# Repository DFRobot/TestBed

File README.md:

TestBed 
=======

Author: Leo Yan.

=======

It is used to test board. It is not a product.

=======
V1.0

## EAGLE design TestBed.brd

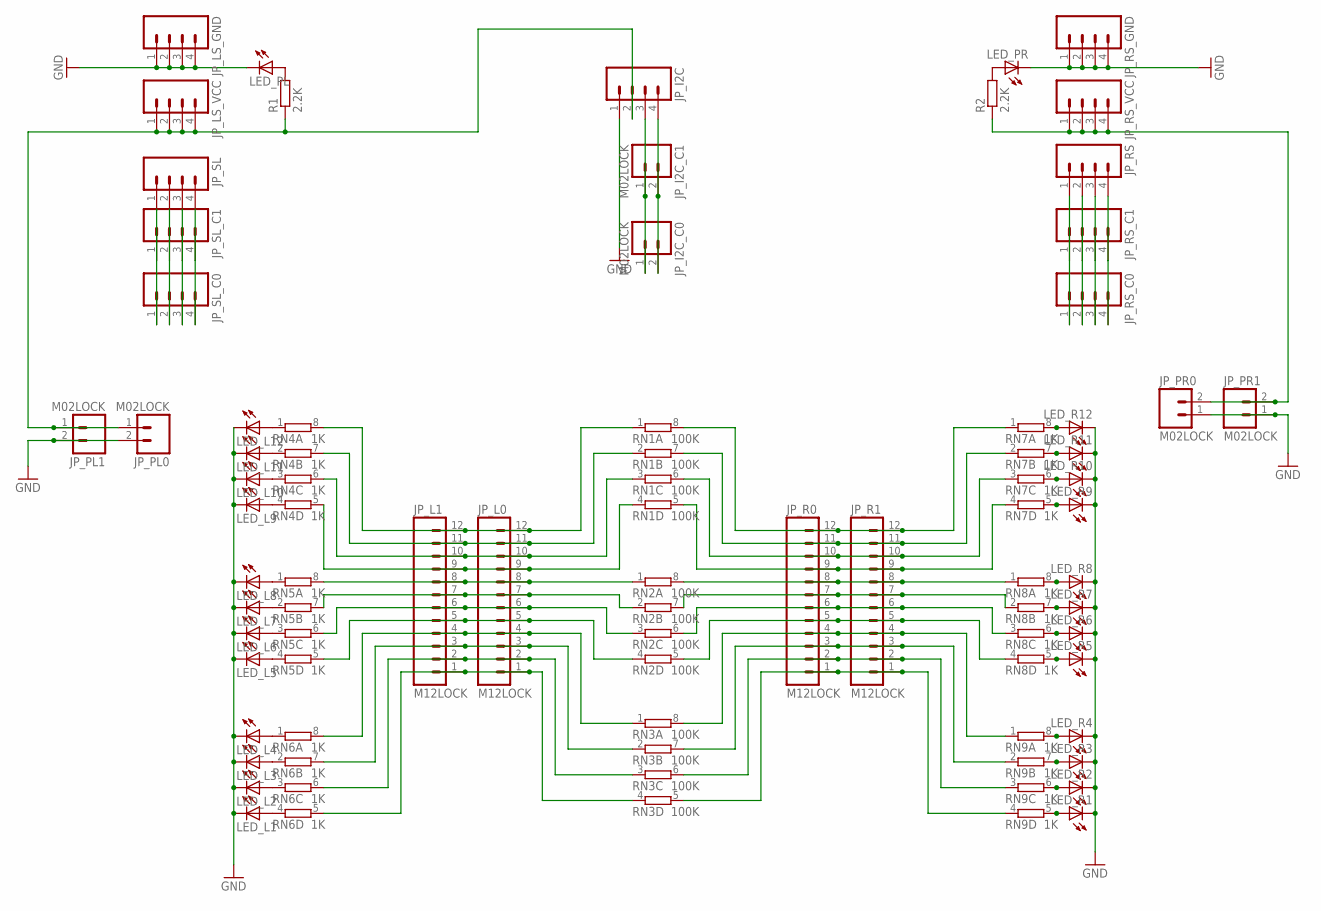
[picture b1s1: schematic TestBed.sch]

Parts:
JP_I2C: M04LOCK; 1X04_LOCK
JP_I2C_C0, JP_I2C_C1: M02LOCK; 1X02_LOCK
JP_L0, JP_L1: M12LOCK; 1X12_LOCK
JP_LS_GND: M04LOCK; 1X04_LOCK
JP_LS_VCC: M04LOCK; 1X04_LOCK
JP_PL0, JP_PL1: M02LOCK; 1X02_LOCK
JP_PR0, JP_PR1: M02LOCK; 1X02_LOCK
JP_R0, JP_R1: M12LOCK; 1X12_LOCK
JP_RS: M04LOCK; 1X04_LOCK
JP_RS_C0, JP_RS_C1: M04LOCK; 1X04_LOCK
JP_RS_GND: M04LOCK; 1X04_LOCK
JP_RS_VCC: M04LOCK; 1X04_LOCK
JP_SL: M04LOCK; 1X04_LOCK
JP_SL_C0, JP_SL_C1: M04LOCK; 1X04_LOCK
LED_L1, LED_L2, LED_L3, LED_L4, LED_L5, LED_L6, LED_L7, LED_L8, LED_L9, LED_L10, LED_L11, LED_L12: LEDCHIP-LED0805; CHIP-LED0805
LED_PL: LEDCHIP-LED0805; CHIP-LED0805
LED_PR: LEDCHIP-LED0805; CHIP-LED0805
LED_R1, LED_R2, LED_R3, LED_R4, LED_R5, LED_R6, LED_R7, LED_R8, LED_R9, LED_R10, LED_R11, LED_R12: LEDCHIP-LED0805; CHIP-LED0805
R1, R2: 2.2K; M0805
RN1, RN2, RN3: 100K; EXBS8V
RN4, RN5, RN6, RN7, RN8, RN9: 1K; EXBS8V

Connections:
GND: JP_I2C.1, JP_LS_GND.1, JP_LS_GND.2, JP_LS_GND.3, JP_LS_GND.4, JP_PL0.2, JP_PL1.2, JP_PR0.1, JP_PR1.1, JP_RS_GND.1, JP_RS_GND.2, JP_RS_GND.3, JP_RS_GND.4, LED_L1.C, LED_L2.C, LED_L3.C, LED_L4.C, LED_L5.C, LED_L6.C, LED_L7.C, LED_L8.C, LED_L9.C, LED_L10.C, LED_L11.C, LED_L12.C, LED_PL.C, LED_PR.C, LED_R1.C, LED_R2.C, LED_R3.C, LED_R4.C, LED_R5.C, LED_R6.C, LED_R7.C, LED_R8.C, LED_R9.C, LED_R10.C, LED_R11.C, LED_R12.C
unnamed: LED_L1.A, RN6.4 (1)
unnamed: LED_L2.A, RN6.3 (1)
unnamed: LED_L3.A, RN6.2 (1)
unnamed: LED_L4.A, RN6.1
unnamed: LED_L5.A, RN5.4 (1)
unnamed: LED_L6.A, RN5.3 (1)
unnamed: LED_L7.A, RN5.2 (1)
unnamed: LED_L8.A, RN5.1
unnamed: LED_L9.A, RN4.4 (1)
unnamed: LED_L10.A, RN4.3 (1)
unnamed: LED_L11.A, RN4.2 (1)
unnamed: LED_L12.A, RN4.1
unnamed: LED_R12.A, RN7.8 (2)
unnamed: LED_R11.A, RN7.7 (2)
unnamed: LED_R10.A, RN7.6 (2)
unnamed: LED_R9.A, RN7.5 (2)
unnamed: LED_R8.A, RN8.8 (2)
unnamed: LED_R7.A, RN8.7 (2)
unnamed: LED_R6.A, RN8.6 (2)
unnamed: LED_R5.A, RN8.5 (2)
unnamed: LED_R4.A, RN9.8 (2)
unnamed: LED_R3.A, RN9.7 (2)
unnamed: LED_R2.A, RN9.6 (2)
unnamed: LED_R1.A, RN9.5 (2)
unnamed: JP_L0.2, JP_L1.2, RN3.3 (1), RN6.6 (2)
unnamed: JP_L0.3, JP_L1.3, RN3.2 (1), RN6.7 (2)
unnamed: JP_L0.1, JP_L1.1, RN3.4 (1), RN6.5 (2)
unnamed: JP_L0.5, JP_L1.5, RN2.4 (1), RN5.5 (2)
unnamed: JP_L0.6, JP_L1.6, RN2.3 (1), RN5.6 (2)
unnamed: JP_L0.7, JP_L1.7, RN2.2 (1), RN5.7 (2)
unnamed: JP_L0.8, JP_L1.8, RN2.1, RN5.8 (2)
unnamed: JP_L0.9, JP_L1.9, RN1.4 (1), RN4.5 (2)
unnamed: JP_R0.12, JP_R1.12, RN1.8 (2), RN7.1
unnamed: JP_L0.11, JP_L1.11, RN1.2 (1), RN4.7 (2)
unnamed: JP_R0.1, JP_R1.1, RN3.5 (2), RN9.4 (1)
unnamed: JP_R0.2, JP_R1.2, RN3.6 (2), RN9.3 (1)
unnamed: JP_R0.3, JP_R1.3, RN3.7 (2), RN9.2 (1)
unnamed: JP_R0.4, JP_R1.4, RN3.8 (2), RN9.1
unnamed: JP_R0.5, JP_R1.5, RN2.5 (2), RN8.4 (1)
unnamed: JP_R0.7, JP_R1.7, RN2.7 (2), RN8.2 (1)
unnamed: JP_SL.1, JP_SL_C0.1, JP_SL_C1.1
unnamed: JP_R0.8, JP_R1.8, RN2.8 (2), RN8.1
unnamed: JP_R0.9, JP_R1.9, RN1.5 (2), RN7.4 (1)
unnamed: JP_R0.10, JP_R1.10, RN1.6 (2), RN7.3 (1)
unnamed: JP_R0.11, JP_R1.11, RN1.7 (2), RN7.2 (1)
unnamed: JP_SL.2, JP_SL_C0.2, JP_SL_C1.2
unnamed: JP_L0.12, JP_L1.12, RN1.1, RN4.8 (2)
unnamed: JP_SL.3, JP_SL_C0.3, JP_SL_C1.3
unnamed: JP_SL.4, JP_SL_C0.4, JP_SL_C1.4
unnamed: JP_L0.4, JP_L1.4, RN3.1, RN6.8 (2)
unnamed: JP_RS.1, JP_RS_C0.1, JP_RS_C1.1
unnamed: JP_RS.2, JP_RS_C0.2, JP_RS_C1.2
unnamed: JP_RS.3, JP_RS_C0.3, JP_RS_C1.3
unnamed: JP_L0.10, JP_L1.10, RN1.3 (1), RN4.6 (2)
unnamed: JP_RS.4, JP_RS_C0.4, JP_RS_C1.4
unnamed: LED_PL.A, R1.2
unnamed: LED_PR.A, R2.2
unnamed: JP_R0.6, JP_R1.6, RN2.6 (2), RN8.3 (1)
SCL: JP_I2C.4, JP_I2C_C0.2, JP_I2C_C1.2
SDA: JP_I2C.3, JP_I2C_C0.1, JP_I2C_C1.1
VCC_L: JP_I2C.2, JP_LS_VCC.1, JP_LS_VCC.2, JP_LS_VCC.3, JP_LS_VCC.4, JP_PL0.1, JP_PL1.1, R1.1
VCC_R: JP_PR0.2, JP_PR1.2, JP_RS_VCC.1, JP_RS_VCC.2, JP_RS_VCC.3, JP_RS_VCC.4, R2.1

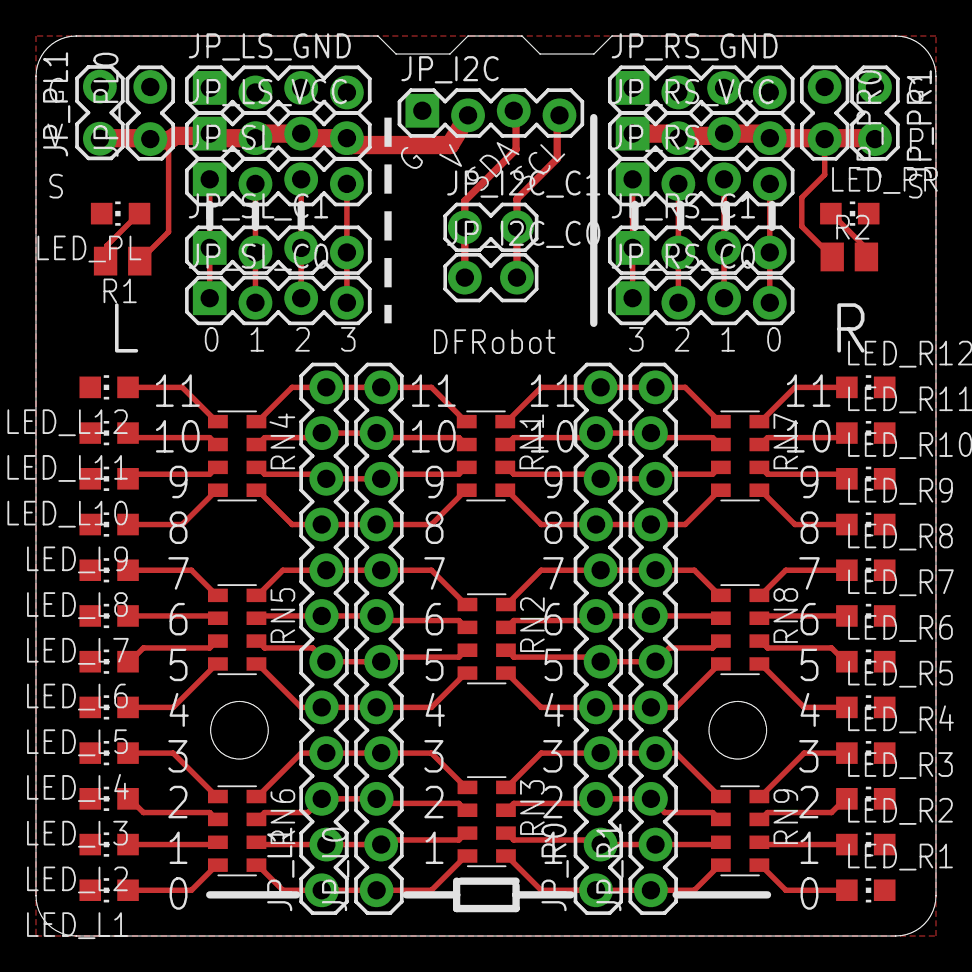
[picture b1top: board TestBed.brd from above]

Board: 2 copper layers, 50.0 x 50.0 mm, 58 parts (0 on the bottom side), 63 nets.

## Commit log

2013-12-05 V1.0

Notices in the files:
parts and their libraries:
SparkFun-Connectors: Licensing: CC v3.0 Share-Alike You are welcome to use this library for commercial purposes.
